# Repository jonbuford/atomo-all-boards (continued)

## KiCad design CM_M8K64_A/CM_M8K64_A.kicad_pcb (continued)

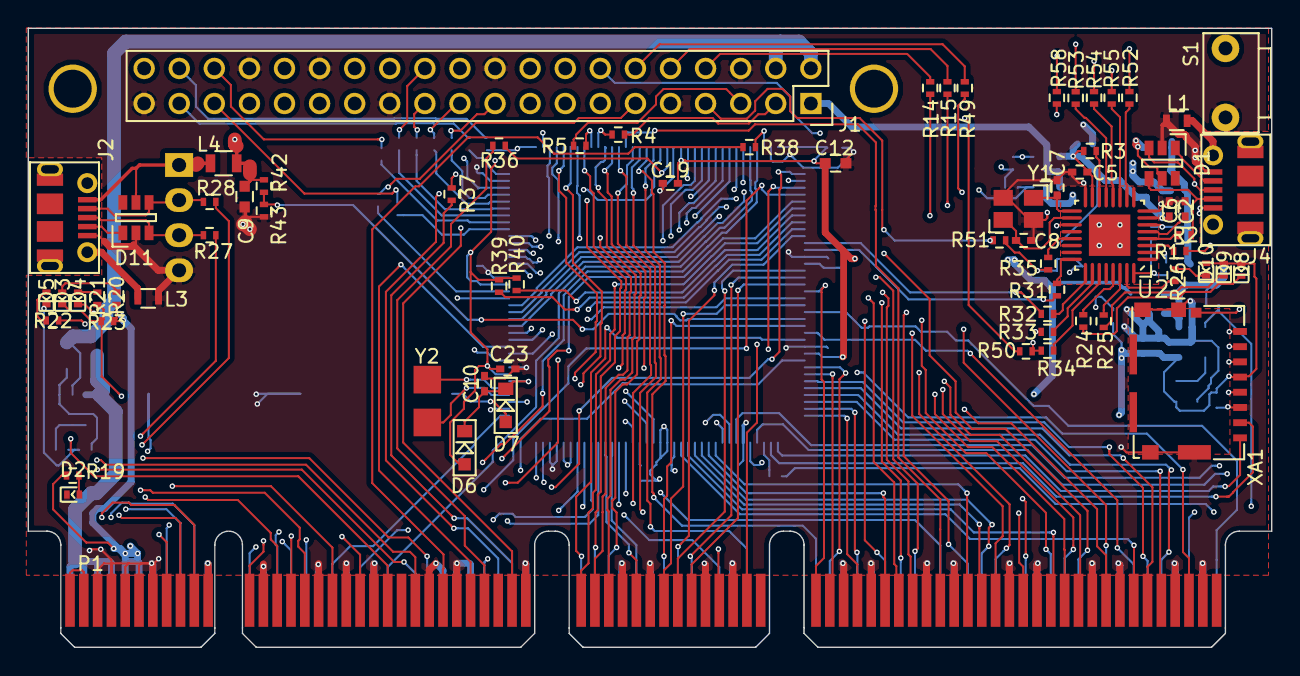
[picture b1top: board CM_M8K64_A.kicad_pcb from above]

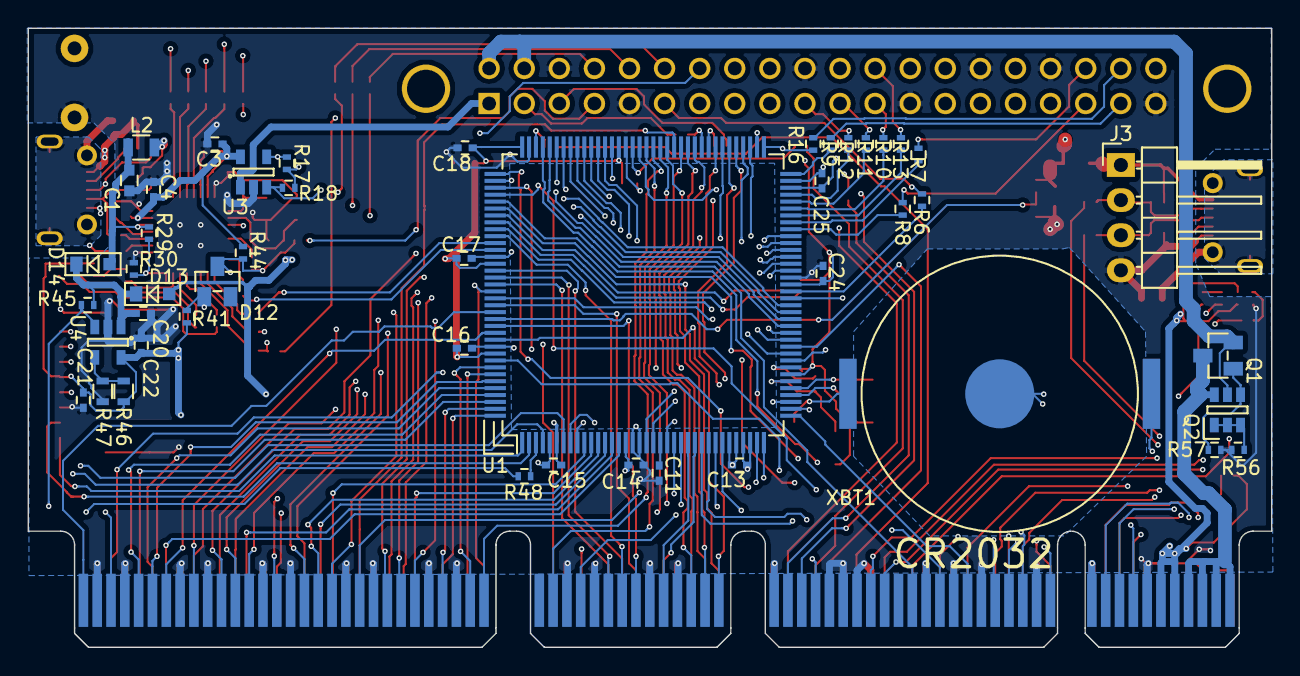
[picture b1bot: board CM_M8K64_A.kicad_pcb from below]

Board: 4 copper layers, 90.0 x 44.8 mm, 117 parts (47 on the bottom side), 197 nets.

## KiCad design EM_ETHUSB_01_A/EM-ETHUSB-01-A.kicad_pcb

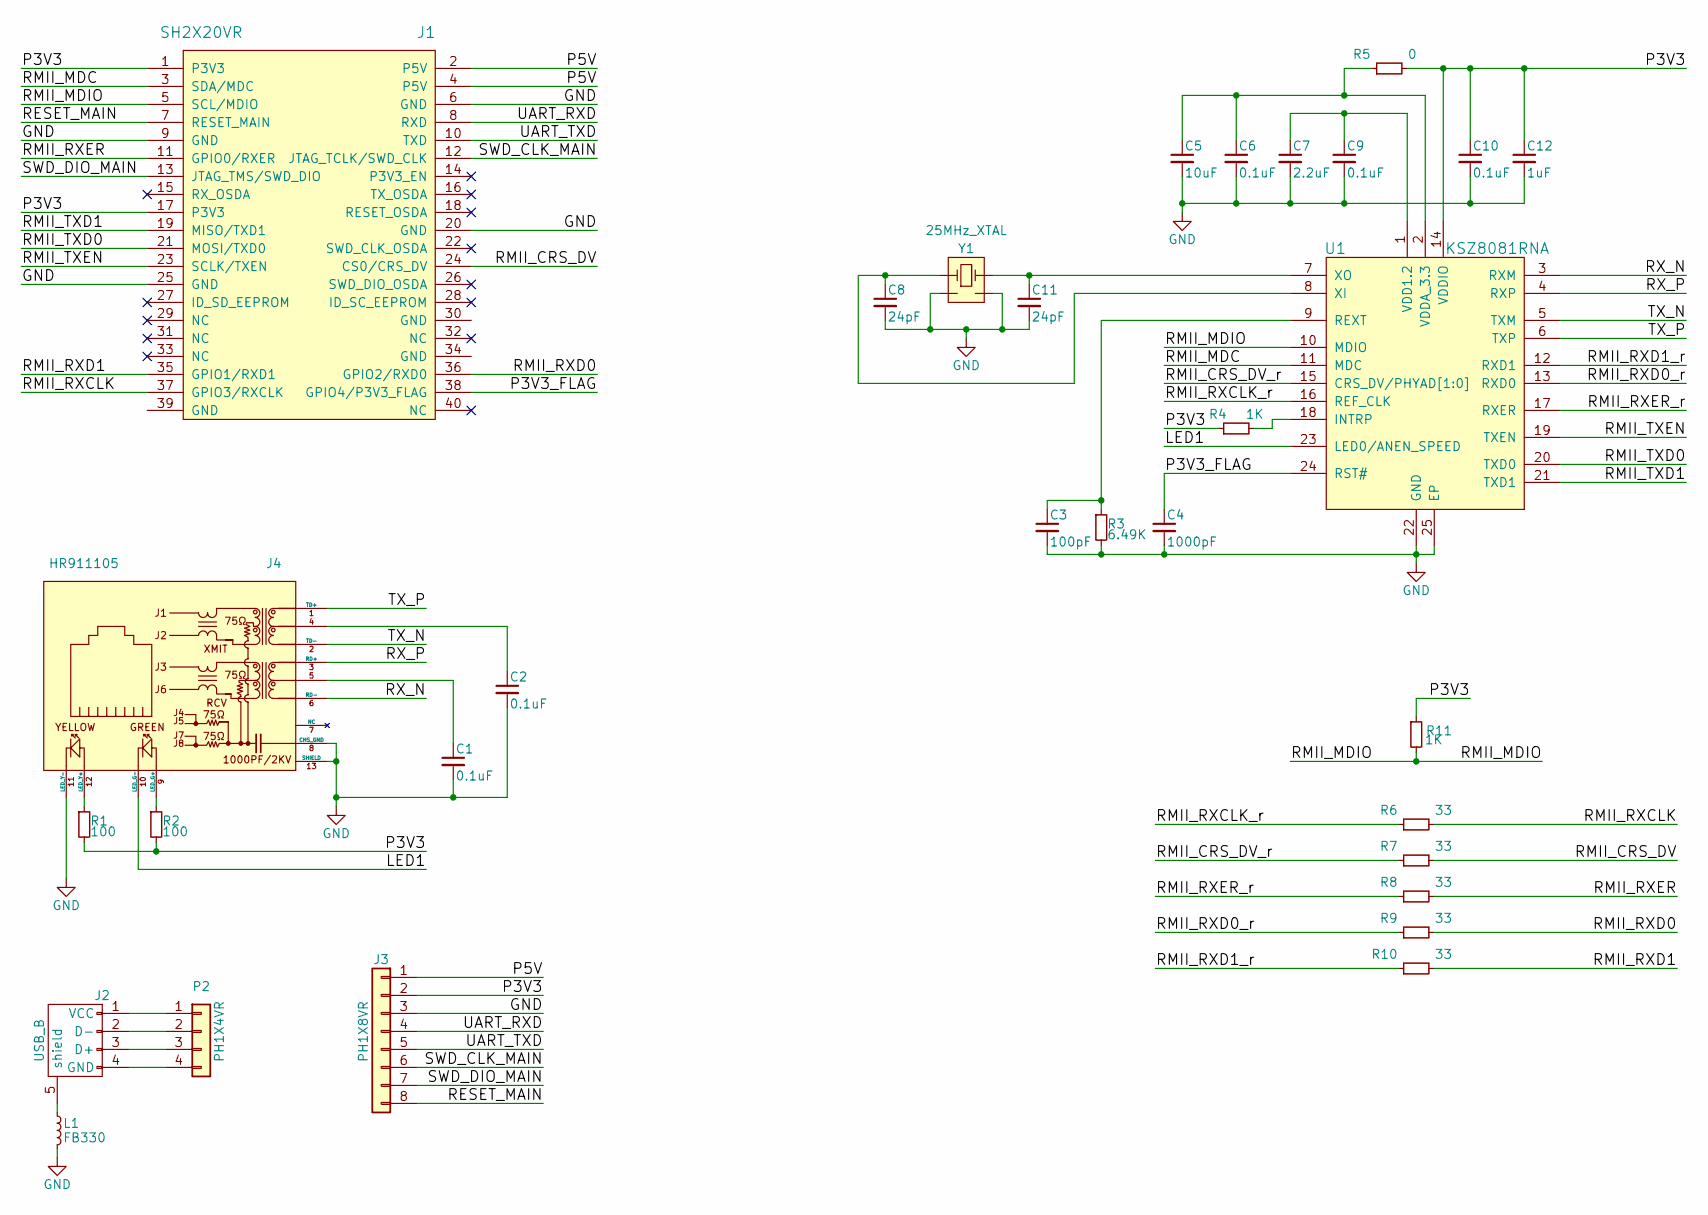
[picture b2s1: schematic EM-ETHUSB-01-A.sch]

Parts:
C1, C2, C6, C9, C10: 0.1uF; C_0402; MPN GRM155R71H104ME14D
C3: 100pF; C_0402; MPN GRM1555C1H101JA01D
C4: 1000pF; C_0402; MPN GRM155R71H102KA01D
C5: 10uF; C_0603; MPN GRM188R60J106KE47D
C7: 2.2uF; C_0402; MPN GRM155R60J225KE95D
C8, C11: 24pF; C_0402; MPN GRM1555C1H240GA01D
C12: 1uF; C_0402; MPN GRM155R60J105KE19D
J1: SH2X20VR; OX40_W_PI_HOLE; MPN PREC020DAAN-RC
J2: USB_B; Molex_67068-003_Full_Size_USB; MPN 670688000
J3: PH1X8VR; Pin_Header_Straight_1x08; MPN DNP
J4: HR911105; HR911105A; MPN HR911105
L1: FB330; R_0603; MPN MPZ1608S331ATA00
P2: PH1X4VR; Pin_Header_Straight_1x04; MPN M20-9990445
R1, R2: 100; R_0402; MPN RC0402JR-07100RL
R3: 6.49K; R_0402; MPN RC0402FR-076K49L
R4, R11: 1K; R_0402; MPN RC0402JR-071KL
R5: 0; R_0402; MPN RC0402JR-070RL
R6, R7, R8, R9, R10: 33; R_0402; MPN RC0402JR-0733RL
U1: KSZ8081RNA; QFN-24-1EP_4x4mm_Pitch0.5mm; MPN KSZ8081RNACA-TR
Y1: 25MHz_XTAL; XTAL3_2X2_5; MPN ABM8G-25.000MHZ-18-D2Y-T

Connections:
/LED1: J4.10 (LED_G-), U1.23 (LED0/ANEN_SPEED)
/P3V3: C10.1, C12.1, J1.1 (P3V3), J1.17 (P3V3), J3.2, R1.2, R2.2, R4.1, R5.2, R11.1, U1.14 (VDDIO)
/P3V3_FLAG: C4.1, J1.38 (GPIO4/P3V3_FLAG), U1.24 (RST#)
/P5V: J1.2 (P5V), J1.4 (P5V), J3.1
/RESET_MAIN: J1.7 (RESET_MAIN), J3.8
/RMII_CRS_DV: J1.24 (CS0/CRS_DV), R7.2
/RMII_CRS_DV_r: R7.1, U1.15 (CRS_DV/PHYAD[1:0])
/RMII_MDC: J1.3 (SDA/MDC), U1.11 (MDC)
/RMII_MDIO: J1.5 (SCL/MDIO), R11.2, U1.10 (MDIO)
/RMII_RXCLK: J1.37 (GPIO3/RXCLK), R6.2
/RMII_RXCLK_r: R6.1, U1.16 (REF_CLK)
/RMII_RXD0: J1.36 (GPIO2/RXD0), R9.2
/RMII_RXD0_r: R9.1, U1.13 (RXD0)
/RMII_RXD1: J1.35 (GPIO1/RXD1), R10.2
/RMII_RXD1_r: R10.1, U1.12 (RXD1)
/RMII_RXER: J1.11 (GPIO0/RXER), R8.2
/RMII_RXER_r: R8.1, U1.17 (RXER)
/RMII_TXD0: J1.21 (MOSI/TXD0), U1.20 (TXD0)
/RMII_TXD1: J1.19 (MISO/TXD1), U1.21 (TXD1)
/RMII_TXEN: J1.23 (SCLK/TXEN), U1.19 (TXEN)
/RX_N: J4.6 (RD-), U1.3 (RXM)
/RX_P: J4.3 (RD+), U1.4 (RXP)
/SWD_CLK_MAIN: J1.12 (JTAG_TCLK/SWD_CLK), J3.6
/SWD_DIO_MAIN: J1.13 (JTAG_TMS/SWD_DIO), J3.7
/TX_N: J4.2 (TD-), U1.5 (TXM)
/TX_P: J4.1 (TD+), U1.6 (TXP)
/UART_RXD: J1.8 (RXD), J3.4
/UART_TXD: J1.10 (TXD), J3.5
GND: C1.2, C2.2, C3.2, C4.2, C5.2, C6.2, C7.2, C8.2, C9.2, C10.2, C11.2, C12.2, J1.6 (GND), J1.9 (GND), J1.20 (GND), J1.25 (GND), J3.3, J4.8 (CHS_GND), J4.11 (LED_Y-), J4.13 (SHIELD), L1.2, R3.2, U1.22 (GND), U1.25 (EP), Y1.2 (GND), Y1.4 (GND)
unnamed: C1.1, J4.5
unnamed: C2.1, J4.4
unnamed: C3.1, R3.1, U1.9 (REXT)
unnamed: C5.1, C6.1, R5.1, U1.2 (VDDA_3.3)
unnamed: C7.1, C9.1, U1.1 (VDD1.2)
unnamed: C8.1, U1.8 (XI), Y1.1
unnamed: C11.1, U1.7 (XO), Y1.3
unnamed: J2.1 (VCC), P2.1
unnamed: J2.2 (D-), P2.2
unnamed: J2.3 (D+), P2.3
unnamed: J2.4 (GND), P2.4
unnamed: J2.5 (shield), L1.1
unnamed: J4.9 (LED_G+), R2.1
unnamed: J4.12 (LED_Y+), R1.1
unnamed: R4.2, U1.18 (INTRP)

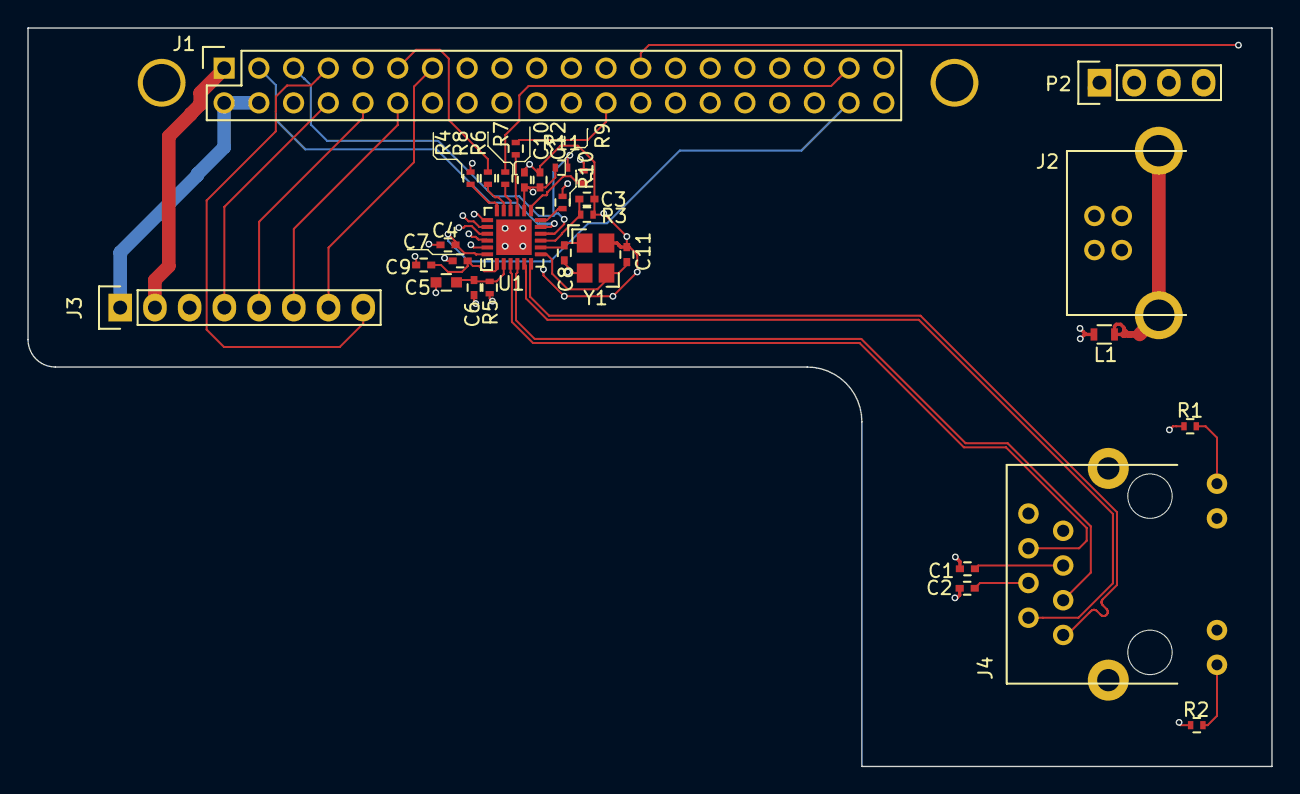
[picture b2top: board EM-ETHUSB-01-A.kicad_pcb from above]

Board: 4 copper layers, 91.0 x 54.0 mm, 31 parts (0 on the bottom side), 44 nets.

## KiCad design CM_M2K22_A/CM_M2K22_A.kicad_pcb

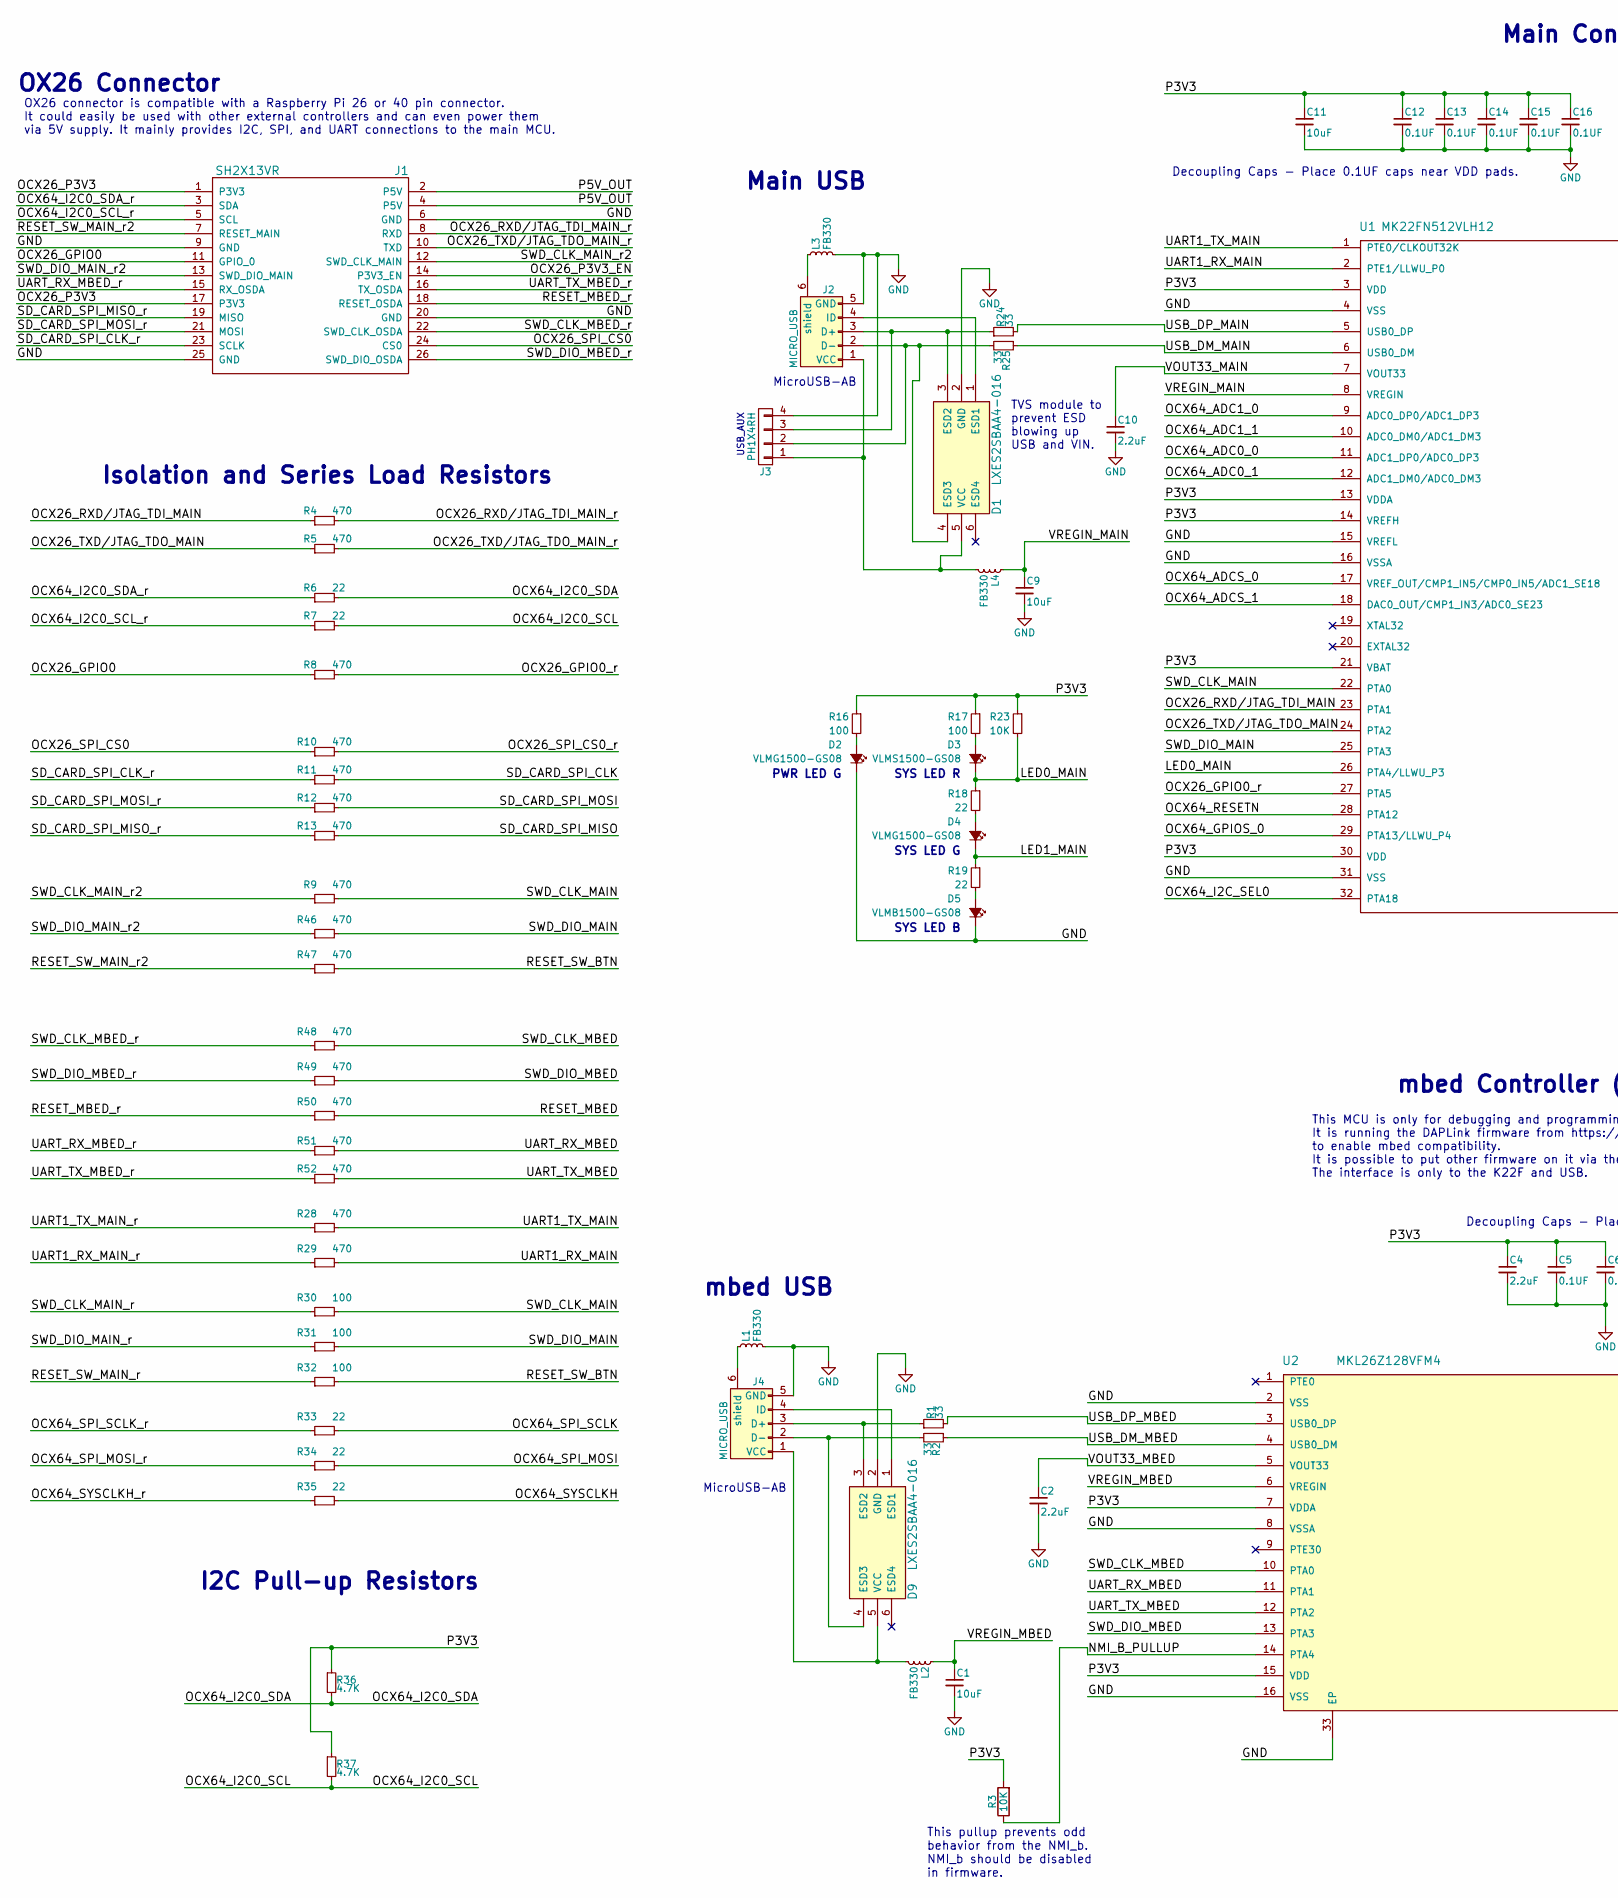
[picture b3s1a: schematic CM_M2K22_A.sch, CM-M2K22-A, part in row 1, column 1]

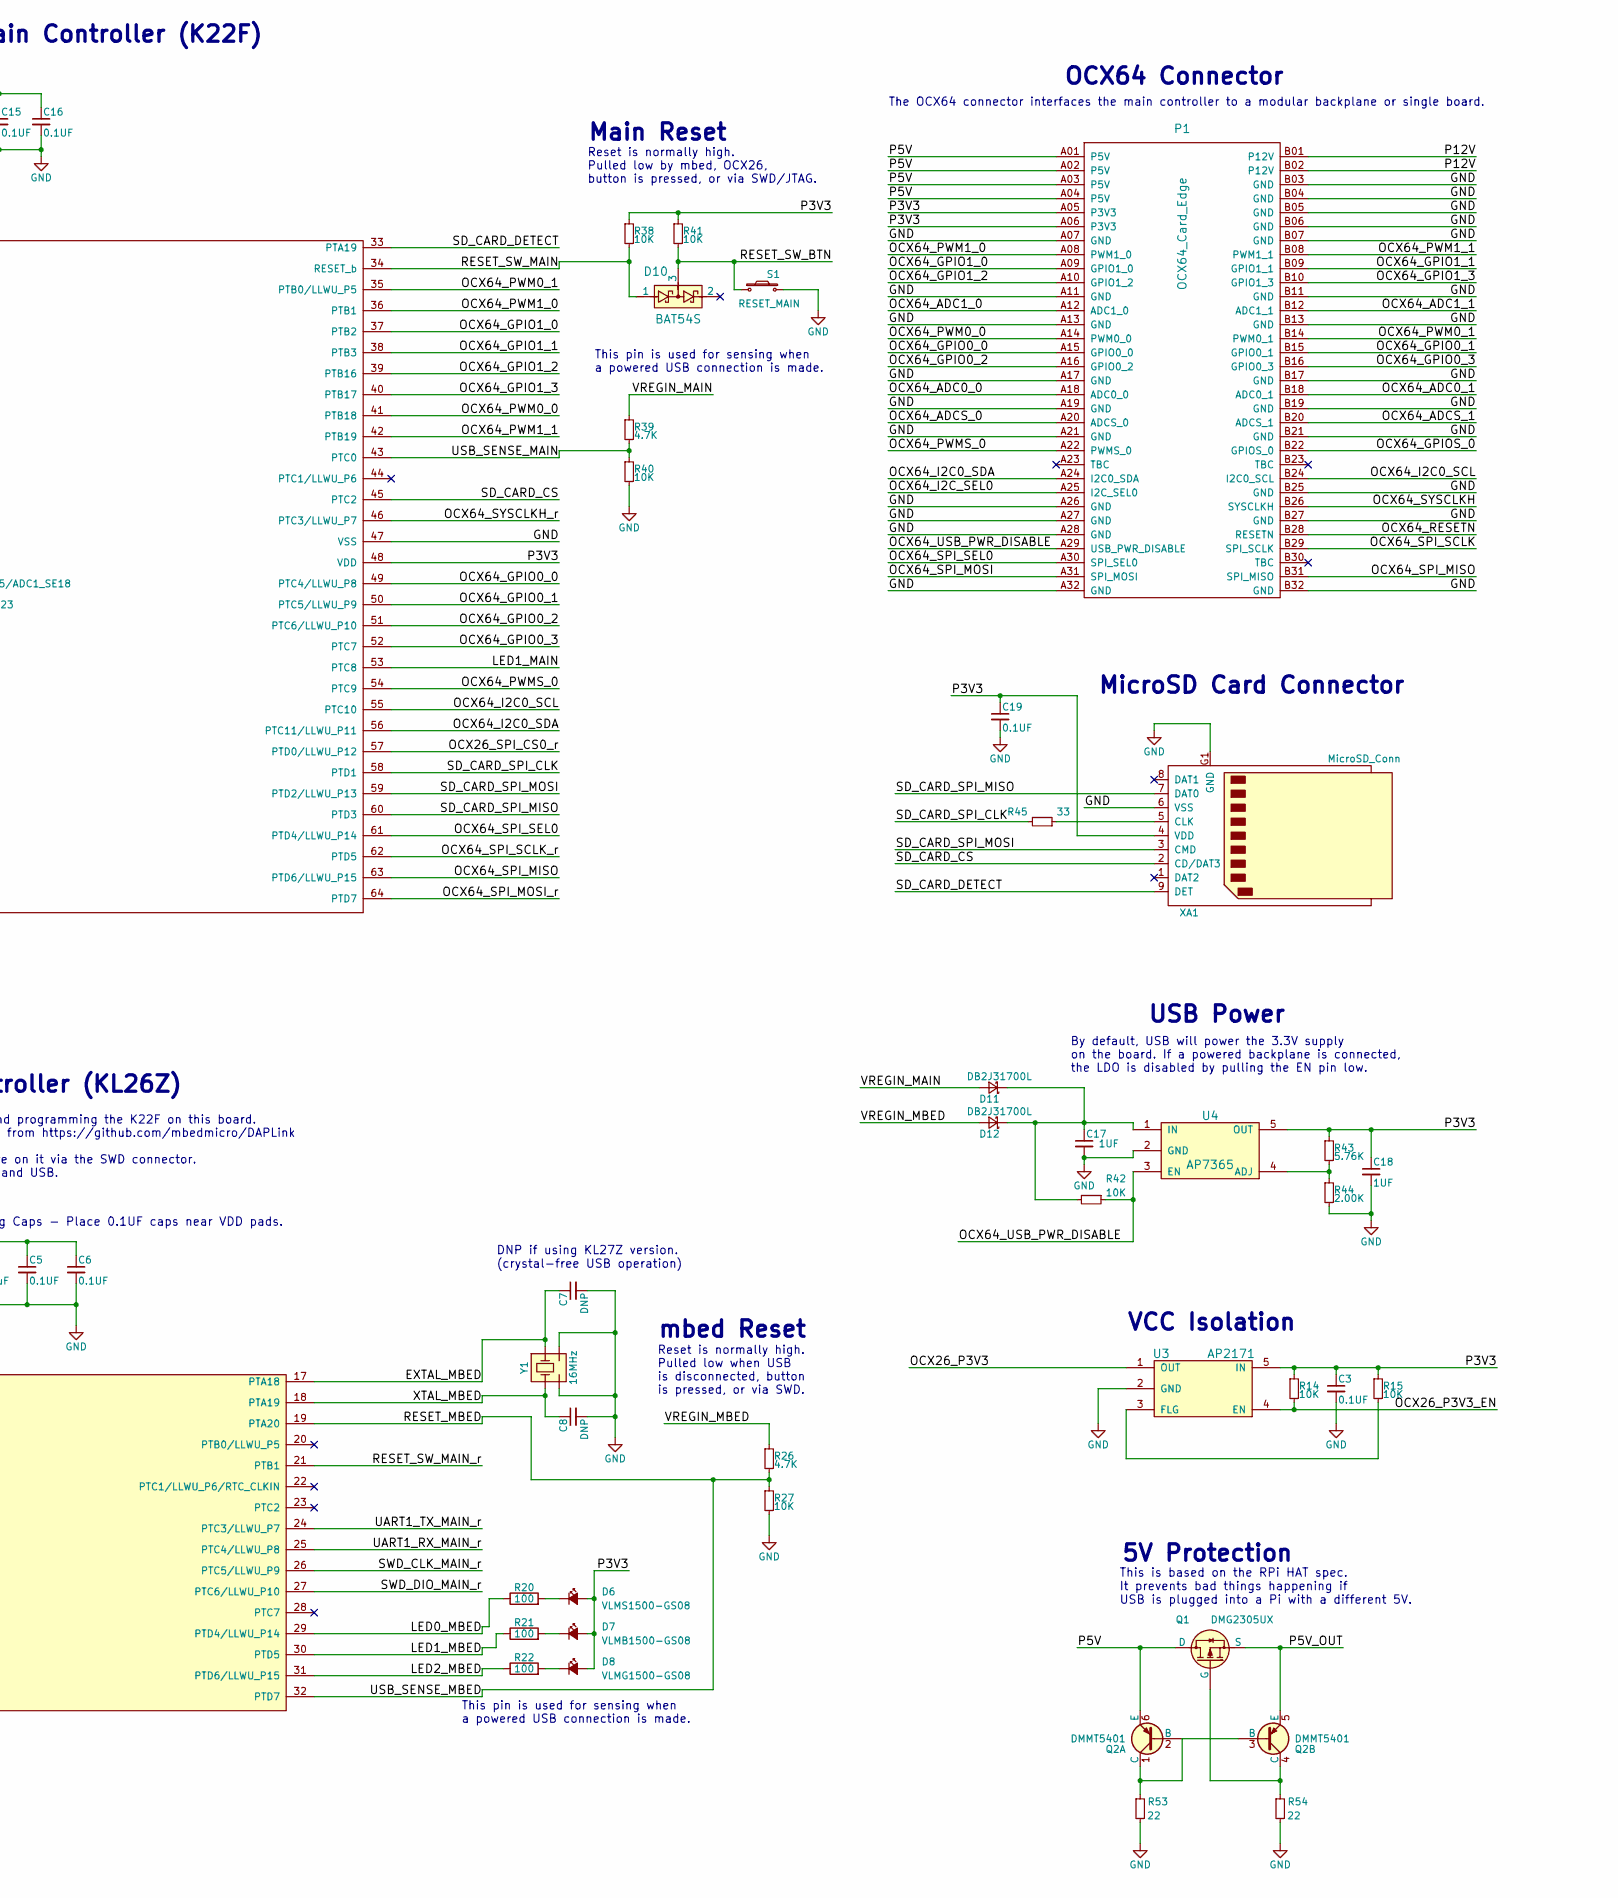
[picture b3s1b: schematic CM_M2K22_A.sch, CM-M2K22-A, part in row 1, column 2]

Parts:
C1, C9, C11: 10uF; C_0603; MPN GRM188R60J106KE47D
C2, C4, C10: 2.2uF; C_0402; MPN GRM155R60J225KE95D
C3, C5, C6, C12, C13, C14, C15, C16, C19: 0.1UF; C_0402; MPN GRM155R71H104ME14D
C7, C8: DNP; C_0402; MPN DNP
C17, C18: 1UF; C_0402; MPN GRM155R60J105KE19D
D1, D9: LXES2SBAA4-016; SOT-23-6; MPN LXES2SBAA4-016
D2, D4, D8: VLMG1500-GS08; LED_0402; MPN VLMG1500-GS08
D3, D6: VLMS1500-GS08; LED_0402; MPN VLMS1500-GS08
D5, D7: VLMB1500-GS08; LED_0402; MPN VLMB1500-GS08
D10: BAT54S; SOT-23; MPN BAT54S,215
D11, D12: DB2J31700L; SC-90A; MPN DB2J31700L
J1: SH2X13VR; OCX26_w_1_Mounting_Hole; MPN PPPC132LFBN-RC
J2, J4: MICRO_USB; Micro_USB_Molex_105017-0001; MPN 1050170001
J3: PH1X4RH; Pin_Header_Angled_1x04; MPN DNP
L1, L3: FB330; R_0603; MPN MPZ1608S331ATA00
L2, L4: FB330; R_0805; MPN MPZ2012S331AT000
P1: OCX64_Card_Edge; MPN DNP
Q1: DMG2305UX; SOT-23; MPN DMG2305UX-13
Q2: DMMT5401; SOT-23-6; MPN DMMT5401-7-F
R1, R2, R24, R25, R45: 33; R_0402; MPN RC0402JR-0733RL
R3, R14, R15, R23, R27, R38, R40, R41, R42: 10K; R_0402; MPN RC0402JR-0710KL
R4, R5, R8, R9, R10, R11, R12, R13, R28, R29, R46, R47, R48, R49, R50, R51, R52: 470; R_0402; MPN RC0402JR-07470RL
R6, R7, R18, R19, R33, R34, R35, R53, R54: 22; R_0402; MPN RC0402JR-0722RL
R16, R17, R20, R21, R22, R30, R31, R32: 100; R_0402; MPN RC0402JR-07100RL
R26, R36, R37, R39: 4.7K; R_0402; MPN RC0402JR-074K7L
R43: 5.76K; R_0603; Tolerance 1%; MPN RC0603FR-075K76L
R44: 2.00K; R_0603; Tolerance 1%; MPN RC0603FR-072KL
S1: RESET_MAIN; Switch_TS-1101F_SZ_BEST; MPN TS-1101F
U1: MK22FN512VLH12; Freescale_LQFP-64; MPN MK22FN512VLH12
U2: MKL26Z128VFM4; QFN32_w_TP_FS; MPN MKL26Z128VFM4
U3: AP2171; SOT-23-5; MPN AP2171WG-7
U4: AP7365; SOT-23-5; MPN AP7365-WG-7
XA1: MicroSD_Conn; 1051620101; MPN 1051620101
Y1: 16MHz; XTAL3_2X2_5; MPN FA-238 16.0000MB-K3

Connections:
/EXTAL_MBED: C7.1, U2.17 (PTA18), Y1.1
/LED0_MAIN: D3.1 (K), R18.1, R23.2, U1.26 (PTA4/LLWU_P3)
/LED0_MBED: R20.1, U2.29 (PTD4/LLWU_P14)
/LED1_MAIN: D4.1 (K), R19.1, U1.53 (PTC8)
/LED1_MBED: R21.1, U2.30 (PTD5)
/LED2_MBED: R22.1, U2.31 (PTD6/LLWU_P15)
/NMI_B_PULLUP: R3.1, U2.14 (PTA4)
/OCX26_GPIO0: J1.11 (GPIO_0), R8.1
/OCX26_GPIO0_r: R8.2, U1.27 (PTA5)
/OCX26_P3V3: J1.1 (P3V3), J1.17 (P3V3), U3.1 (OUT)
/OCX26_P3V3_EN: J1.14 (P3V3_EN), R14.2, U3.4 (EN)
/OCX26_RXD/JTAG_TDI_MAIN: R4.1, U1.23 (PTA1)
/OCX26_RXD/JTAG_TDI_MAIN_r: J1.8 (RXD), R4.2
/OCX26_SPI_CS0: J1.24 (CS0), R10.1
/OCX26_SPI_CS0_r: R10.2, U1.57 (PTD0/LLWU_P12)
/OCX26_TXD/JTAG_TDO_MAIN: R5.1, U1.24 (PTA2)
/OCX26_TXD/JTAG_TDO_MAIN_r: J1.10 (TXD), R5.2
/OCX64_ADC0_0: P1.A18 (ADC0_0), U1.11 (ADC1_DP0/ADC0_DP3)
/OCX64_ADC0_1: P1.B18 (ADC0_1), U1.12 (ADC1_DM0/ADC0_DM3)
/OCX64_ADC1_0: P1.A12 (ADC1_0), U1.9 (ADC0_DP0/ADC1_DP3)
/OCX64_ADC1_1: P1.B12 (ADC1_1), U1.10 (ADC0_DM0/ADC1_DM3)
/OCX64_ADCS_0: P1.A20 (ADCS_0), U1.17 (VREF_OUT/CMP1_IN5/CMP0_IN5/ADC1_SE18)
/OCX64_ADCS_1: P1.B20 (ADCS_1), U1.18 (DAC0_OUT/CMP1_IN3/ADC0_SE23)
/OCX64_GPIO0_0: P1.A15 (GPIO0_0), U1.49 (PTC4/LLWU_P8)
/OCX64_GPIO0_1: P1.B15 (GPIO0_1), U1.50 (PTC5/LLWU_P9)
/OCX64_GPIO0_2: P1.A16 (GPIO0_2), U1.51 (PTC6/LLWU_P10)
/OCX64_GPIO0_3: P1.B16 (GPIO0_3), U1.52 (PTC7)
/OCX64_GPIO1_0: P1.A09 (GPIO1_0), U1.37 (PTB2)
/OCX64_GPIO1_1: P1.B09 (GPIO1_1), U1.38 (PTB3)
/OCX64_GPIO1_2: P1.A10 (GPIO1_2), U1.39 (PTB16)
/OCX64_GPIO1_3: P1.B10 (GPIO1_3), U1.40 (PTB17)
/OCX64_GPIOS_0: P1.B22 (GPIOS_0), U1.29 (PTA13/LLWU_P4)
/OCX64_I2C0_SCL: P1.B24 (I2C0_SCL), R7.2, R37.2, U1.55 (PTC10)
/OCX64_I2C0_SCL_r: J1.5 (SCL), R7.1
/OCX64_I2C0_SDA: P1.A24 (I2C0_SDA), R6.2, R36.2, U1.56 (PTC11/LLWU_P11)
/OCX64_I2C0_SDA_r: J1.3 (SDA), R6.1
/OCX64_I2C_SEL0: P1.A25 (I2C_SEL0), U1.32 (PTA18)
/OCX64_PWM0_0: P1.A14 (PWM0_0), U1.41 (PTB18)
/OCX64_PWM0_1: P1.B14 (PWM0_1), U1.35 (PTB0/LLWU_P5)
/OCX64_PWM1_0: P1.A08 (PWM1_0), U1.36 (PTB1)
/OCX64_PWM1_1: P1.B08 (PWM1_1), U1.42 (PTB19)
/OCX64_PWMS_0: P1.A22 (PWMS_0), U1.54 (PTC9)
/OCX64_RESETN: P1.B28 (RESETN), U1.28 (PTA12)
/OCX64_SPI_MISO: P1.B31 (SPI_MISO), U1.63 (PTD6/LLWU_P15)
/OCX64_SPI_MOSI: P1.A31 (SPI_MOSI), R34.2
/OCX64_SPI_MOSI_r: R34.1, U1.64 (PTD7)
/OCX64_SPI_SCLK: P1.B29 (SPI_SCLK), R33.2
/OCX64_SPI_SCLK_r: R33.1, U1.62 (PTD5)
/OCX64_SPI_SEL0: P1.A30 (SPI_SEL0), U1.61 (PTD4/LLWU_P14)
/OCX64_SYSCLKH: P1.B26 (SYSCLKH), R35.2
/OCX64_SYSCLKH_r: R35.1, U1.46 (PTC3/LLWU_P7)
/OCX64_USB_PWR_DISABLE: P1.A29 (USB_PWR_DISABLE), R42.1, U4.3 (EN)
/P3V3: C3.1, C4.1, C5.1, C6.1, C11.1, C12.1, C13.1, C14.1, C15.1, C16.1, C18.1, C19.1, D6.2 (A), D7.2 (A), D8.2 (A), P1.A05 (P3V3), P1.A06 (P3V3), R3.2, R14.1, R15.1, R16.1, R17.1, R23.1, R36.1, R37.1, R38.1, R41.1, R43.1, U1.3 (VDD), U1.13 (VDDA), U1.14 (VREFH), U1.21 (VBAT), U1.30 (VDD), U1.48 (VDD), U2.7 (VDDA), U2.15 (VDD), U3.5 (IN), U4.5 (OUT), XA1.4 (VDD)
/P5V: P1.A01 (P5V), P1.A02 (P5V), P1.A03 (P5V), P1.A04 (P5V), Q1.3 (D), Q2.6 (E)
/P5V_OUT: J1.2 (P5V), J1.4 (P5V), Q1.2 (S), Q2.5 (E)
/P12V: P1.B01 (P12V), P1.B02 (P12V)
/RESET_MBED: R26.2, R27.1, R50.2, U2.19 (PTA20), U2.32 (PTD7)
/RESET_MBED_r: J1.18 (RESET_OSDA), R50.1
/RESET_SW_BTN: D10.3, R32.2, R41.2, R47.2, S1.1
/RESET_SW_MAIN: D10.1, R38.2, U1.34 (RESET_b)
/RESET_SW_MAIN_r: R32.1, U2.21 (PTB1)
/RESET_SW_MAIN_r2: J1.7 (RESET_MAIN), R47.1
/SD_CARD_CS: U1.45 (PTC2), XA1.2 (CD/DAT3)
/SD_CARD_DETECT: U1.33 (PTA19), XA1.9 (DET)
/SD_CARD_SPI_CLK: R11.2, R45.2, U1.58 (PTD1)
/SD_CARD_SPI_CLK_r: J1.23 (SCLK), R11.1
/SD_CARD_SPI_MISO: R13.2, U1.60 (PTD3), XA1.7 (DAT0)
/SD_CARD_SPI_MISO_r: J1.19 (MISO), R13.1
/SD_CARD_SPI_MOSI: R12.2, U1.59 (PTD2/LLWU_P13), XA1.3 (CMD)
/SD_CARD_SPI_MOSI_r: J1.21 (MOSI), R12.1
/SWD_CLK_MAIN: R9.2, R30.2, U1.22 (PTA0)
/SWD_CLK_MAIN_r: R30.1, U2.26 (PTC5/LLWU_P9)
/SWD_CLK_MAIN_r2: J1.12 (SWD_CLK_MAIN), R9.1
/SWD_CLK_MBED: R48.2, U2.10 (PTA0)
/SWD_CLK_MBED_r: J1.22 (SWD_CLK_OSDA), R48.1
/SWD_DIO_MAIN: R31.2, R46.2, U1.25 (PTA3)
/SWD_DIO_MAIN_r: R31.1, U2.27 (PTC6/LLWU_P10)
/SWD_DIO_MAIN_r2: J1.13 (SWD_DIO_MAIN), R46.1
/SWD_DIO_MBED: R49.2, U2.13 (PTA3)
/SWD_DIO_MBED_r: J1.26 (SWD_DIO_OSDA), R49.1
/UART1_RX_MAIN: R29.2, U1.2 (PTE1/LLWU_P0)
/UART1_RX_MAIN_r: R29.1, U2.25 (PTC4/LLWU_P8)
/UART1_TX_MAIN: R28.2, U1.1 (PTE0/CLKOUT32K)
/UART1_TX_MAIN_r: R28.1, U2.24 (PTC3/LLWU_P7)
/UART_RX_MBED: R51.2, U2.11 (PTA1)
/UART_RX_MBED_r: J1.15 (RX_OSDA), R51.1
/UART_TX_MBED: R52.2, U2.12 (PTA2)
/UART_TX_MBED_r: J1.16 (TX_OSDA), R52.1
/USB_DM_MAIN: R25.1, U1.6 (USB0_DM)
/USB_DM_MBED: R2.1, U2.4 (USB0_DM)
/USB_DP_MAIN: R24.2, U1.5 (USB0_DP)
/USB_DP_MBED: R1.2, U2.3 (USB0_DP)
/USB_SENSE_MAIN: R39.2, R40.1, U1.43 (PTC0)
/VOUT33_MAIN: C10.1, U1.7 (VOUT33)
/VOUT33_MBED: C2.1, U2.5 (VOUT33)
/VREGIN_MAIN: C9.1, D11.2 (A), L4.1, R39.1, U1.8 (VREGIN)
/VREGIN_MBED: C1.1, D12.2 (A), L2.1, R26.1, U2.6 (VREGIN)
/XTAL_MBED: C8.1, U2.18 (PTA19), Y1.3
GND: C1.2, C2.2, C3.2, C4.2, C5.2, C6.2, C7.2, C8.2, C9.2, C10.2, C11.2, C12.2, C13.2, C14.2, C15.2, C16.2, C17.2, C18.2, C19.2, D1.2 (GND), D2.1 (K), D5.1 (K), D9.2 (GND), J1.6 (GND), J1.9 (GND), J1.20 (GND), J1.25 (GND), J2.5 (GND), J3.4, J4.5 (GND), L1.2, L3.2, P1.A07 (GND), P1.A11 (GND), P1.A13 (GND), P1.A17 (GND), P1.A19 (GND), P1.A21 (GND), P1.A26 (GND), P1.A27 (GND), P1.A28 (GND), P1.A32 (GND), P1.B03 (GND), P1.B04 (GND), P1.B05 (GND), P1.B06 (GND), P1.B07 (GND), P1.B11 (GND), P1.B13 (GND), P1.B17 (GND), P1.B19 (GND), P1.B21 (GND), P1.B25 (GND), P1.B27 (GND), P1.B32 (GND), R27.2, R40.2, R44.2, R53.2, R54.2, S1.2, U1.4 (VSS), U1.15 (VREFL), U1.16 (VSSA), U1.31 (VSS), U1.47 (VSS), U2.2 (VSS), U2.8 (VSSA), U2.16 (VSS), U2.33 (EP), U3.2 (GND), U4.2 (GND), XA1.6 (VSS), XA1.G1 (GND), XA1.G2 (GND), XA1.G3 (GND), XA1.G4 (GND), Y1.2 (GND), Y1.4 (GND)
unnamed: C17.1, D11.1 (K), D12.1 (K), R42.2, U4.1 (IN)
unnamed: D1.1 (ESD1), J2.4 (ID)
unnamed: D1.3 (ESD2), J2.3 (D+), J3.3, R24.1
unnamed: D1.4 (ESD3), J2.2 (D-), J3.2, R25.2
unnamed: D1.5 (VCC), J2.1 (VCC), J3.1, L4.2
unnamed: D2.2 (A), R16.2
unnamed: D3.2 (A), R17.2
unnamed: D4.2 (A), R18.2
unnamed: D5.2 (A), R19.2
unnamed: D6.1 (K), R20.2
unnamed: D7.1 (K), R21.2
unnamed: D8.1 (K), R22.2
unnamed: D9.1 (ESD1), J4.4 (ID)
unnamed: D9.3 (ESD2), J4.3 (D+), R1.1
unnamed: D9.4 (ESD3), J4.2 (D-), R2.2
unnamed: D9.5 (VCC), J4.1 (VCC), L2.2
unnamed: J2.6 (shield), L3.1
unnamed: J4.6 (shield), L1.1
unnamed: Q1.1 (G), Q2.4 (C), R54.1
unnamed: Q2.1 (C), Q2.2 (B), Q2.3 (B), R53.1
unnamed: R15.2, U3.3 (FLG)
unnamed: R43.2, R44.1, U4.4 (ADJ)
unnamed: R45.1, XA1.5 (CLK)

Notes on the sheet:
Decoupling Caps - Place 0.1UF caps near VDD pads.
OX26 Connector
mbed Controller (KL26Z)
Main Controller (K22F)
OCX64 Connector
This pin is used for sensing when a powered USB connection is made.
TVS module to prevent ESD blowing up USB and VIN.
MicroUSB-AB
MicroSD Card Connector
Main USB
mbed USB
Main Reset
mbed Reset
Reset is normally high. Pulled low when USB is disconnected, button is pressed, or via SWD.
Reset is normally high. Pulled low by mbed, OCX26, button is pressed, or via SWD/JTAG.
SYS LED B
SYS LED R
SYS LED G
OX26 connector is compatible with a Raspberry Pi 26 or 40 pin connector. It could easily be used with other external controllers and can even power them via 5V supply. It mainly provides I2C, SPI, and UART connections to the main MCU.
The OCX64 connector interfaces the main controller to a modular backplane or single board.
This MCU is only for debugging and programming the K22F on this board. It is running the DAPLink firmware from https://github.com/mbedmicro/DAPLink to enable mbed compatibility. It is possible to put other firmware on it via the SWD connector. The interface is only to the K22F and USB.
This pullup prevents odd behavior from the NMI_b. NMI_b should be disabled in firmware.
USB Power
By default, USB will power the 3.3V supply on the board. If a powered backplane is connected, the LDO is disabled by pulling the EN pin low.
I2C Pull-up Resistors
DNP if using KL27Z version. (crystal-free USB operation)
Isolation and Series Load Resistors
VCC Isolation
PWR LED G
USB_AUX
5V Protection
This is based on the RPi HAT spec. It prevents bad things happening if USB is plugged into a Pi with a different 5V.

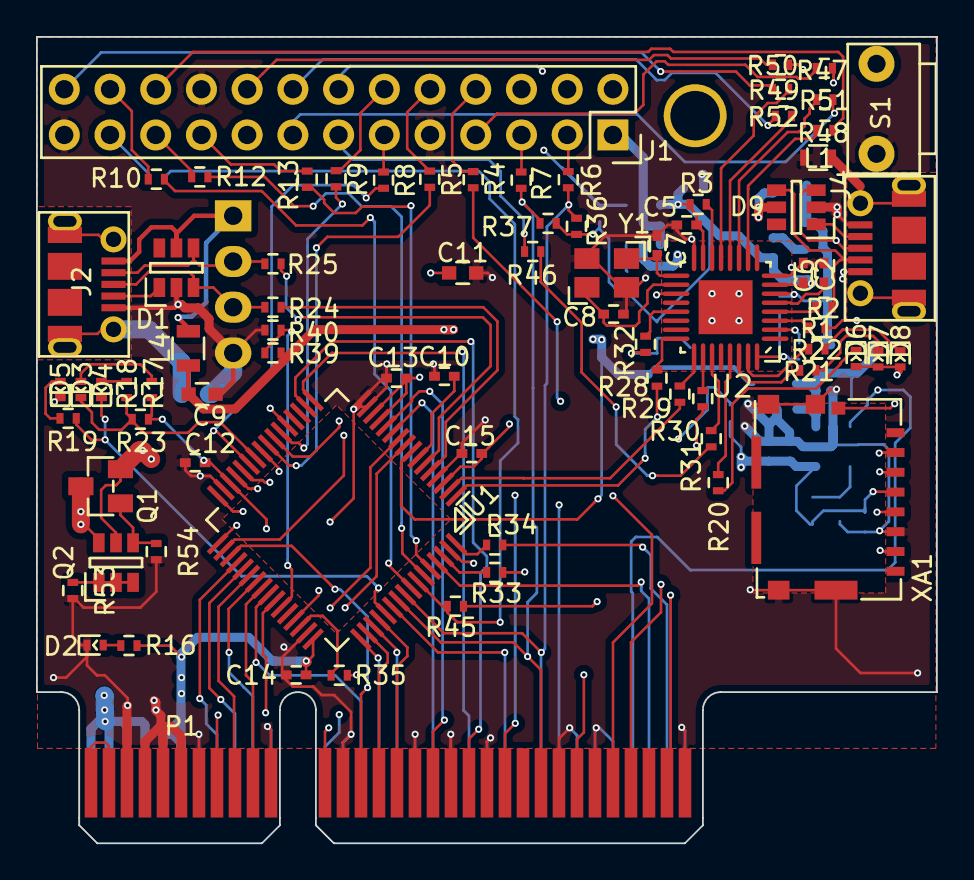
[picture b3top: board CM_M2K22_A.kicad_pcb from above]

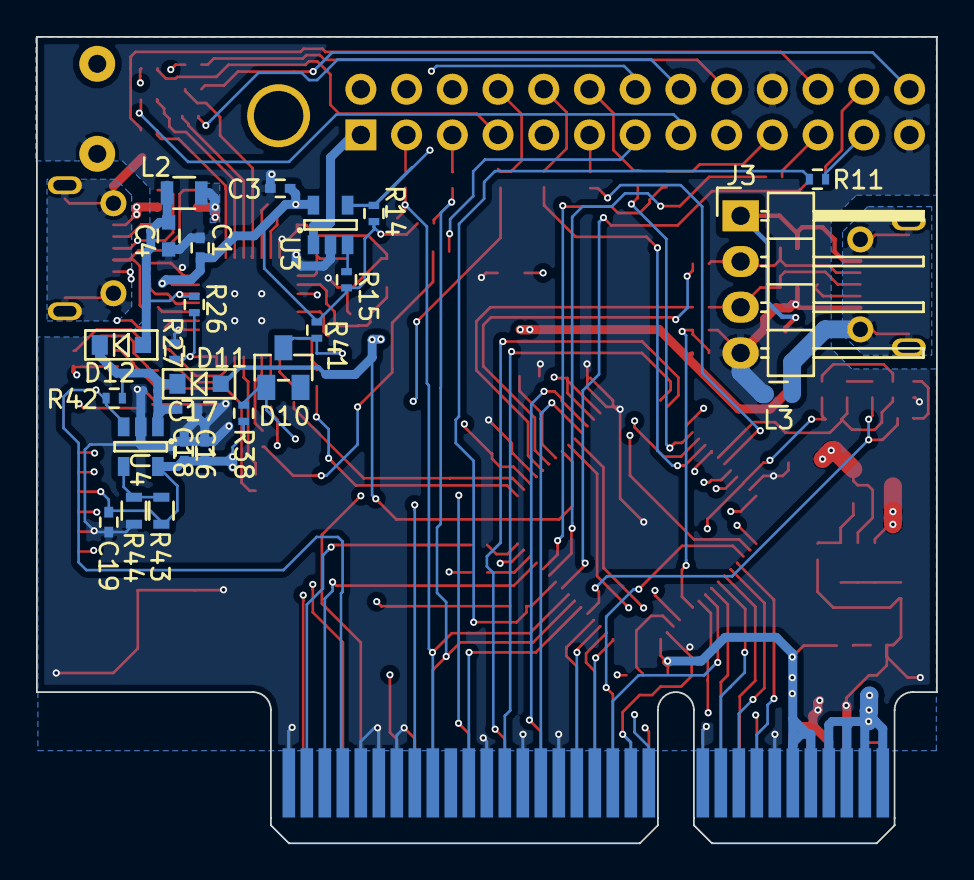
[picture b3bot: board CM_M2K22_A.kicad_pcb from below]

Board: 4 copper layers, 50.0 x 44.8 mm, 103 parts (25 on the bottom side), 122 nets.

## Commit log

2017-09-26 Updating Readme
    This is just a quick update on the current status and outlining the major changes in the last couple of months.
2017-09-26 Updating gitignore
    Skipping the production silk files.
2017-09-26 Initial Commit
    This is the current production ready files (still needs final silk) for
    release.
